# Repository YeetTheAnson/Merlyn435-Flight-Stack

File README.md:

# Merlyn435 Flight Stack

## Introduction
This is my custom Merlyn435 Flight Stack! This project was made as a successor to my previous Merlyn411 flight controller due to several limitations. It lacked in its processing power and free UART ports. Its mounting pattern was also unconventional at 25mm, making its mounting incompatible with any ESCs on the market. By upgrading to the AT32F435@288MHz, the new Merlyn435 easily handles 8k8 PID loop and advanced autonomous flights with 3 spare UART ports.

The Merlyn435 also upgrades the IMU from the MPU6500 to the LSM6DSK320X, which provides significantly better vibration noise rejection at $3.8\ \mathrm{mdps}/\sqrt{\mathrm{Hz}}$ compared to $10\ \mathrm{mdps}/\sqrt{\mathrm{Hz}}$. This results in cooler motors and more stable flights with fewer gyro filters, preventing issues such as mid throttle oscillation and flyaways.

The Merlyn435 flight controller is designed for a wide battery voltage ranging from 2 to 6 cells. This flight controller can also be mounted in various sizes of drones from 2" to as big as it can get.

It is a 3 in 1 flight controller offers features such as an integrated 2.4GHz ExpressLRS receiver and an OSD to overlay telemetry directly in the video feed. Furthermore, it has 16MB of flash memory for blackbox logging to assist in flight tuning.

The MerlynESC is a 4 in 1 ESC which runs on Bluejay firmware and also operates from 2 to 6s battery voltages. Its maximum continuous current is 40A per motor and peaks up to 55A for a maximum duration of 10 seconds.

| Feature | Merlyn435 | Merlyn411 |
|---|---|---|
| **MCU** | AT32F435CGU7 @ 288MHz | STM32F411CEU6 @ 100MHz |
| **MCU Flash Size** | 1024kB | 512kB |
| **UART Interfaces** | 5 Hardware UART (2 internal, 3 free) | 2 Hardware UART + 1 SoftSerial (1 internal, 1 softserial, 1 free) |
| **IMU** | LSM6DSK320X (SPI) | MPU6500 (SPI) |
| **Barometer** | BMP388 (I2C) | None |
| **OSD** | AT7456E (SPI) | AT7456E (SPI) |
| **Blackbox Flash** | 16MB (SPI) | 16MB (SPI) |
| **Integrated Receiver** | Serial ExpressLRS 2.4GHz  | Serial ExpressLRS 2.4GHz |
| **Mounting Size** | M2 20x20mm | M2 25.5x25.5mm |
| **BEC** | 5V 2A @ 1.1MHz Synchronous | 5V 2A @ 150kHz Asynchronous |
| **ESC Connection** | 8 pin JST-SH (Betaflight standard) | Direct solder pads |

## Hardware Specifications

### Merlyn435
* **MCU:** AT32F435CGU7
* **IMU:** LSM6DSK320X @ SPI1
* **Barometer:** BMP388 @ 0x76
* **OSD:** AT7456E @ SPI2
* **Blackbox:** W25Q128JV 16MB Flash @ SPI2
* **Receiver:** Serial ExpressLRS (ESP8285 + SX1281) @ UART2
* **Voltage range:** 2-6s LiPo / Li-ion / LiHV
* **Power Supply:** LMR51420YDDCR buck converter + SPX3819M5-L-3-3 LDO
* **Mounting:** M2 20x20mm

### MerlynESC
* **MCU:** EFM8BB21F16G
* **MOSFET:** JMSL0302AU
* **Gate Driver:** EG6288
* **Max Current:** 145A Peak / 40A Continuous @ 1.2mΩ
* **Voltage range:** 2-6s LiPo / Li-ion / LiHV
* **Power Supply:** HT75C0-1 12V LDO + HT7533-1 3.3V LDO
* **Mounting:** M2 20x20mm

## Pinout

| Header | Pin name | AT32 Pin | Description |
|---|---|---|---|
| **ESC** | `(1)BAT+` | - | Battery Positive Input from ESC |
| | `(2)GND` | - | Ground |
| | `(3)NC` | - | No Connection |
| | `(4)CURR` | PA1 | Current Sense Input |
| | `(5)M1` | PB6 | Motor 1 Signal Output |
| | `(6)M2` | PB7 | Motor 2 Signal Output |
| | `(7)M3` | PB0 | Motor 3 Signal Output |
| | `(8)M4` | PB1 | Motor 4 Signal Output |
| **GPS** | `C` | PH2 | I2C SCL (Internal BMP388 & External Magnetometer) |
| | `D` | PH3 | I2C SDA (Internal BMP388 & External Magnetometer) |
| | `T` | PB4 | UART7 TX |
| | `R` | PB3 | UART7 RX |
| | `G` | - | Ground |
| | `5` | - | 5V Power Output |
| **URT5** | `T` | PB9 | UART5 TX |
| | `R` | PB8 | UART5 RX |
| | `G` | - | Ground |
| | `5` | - | 5V Power Output |
| **CAM** | `I` | - | Analog Video Input |
| | `G` | - | Ground |
| | `5` | - | 5V Power Output |
| **URT3** | `5` | - | 5V Power Output |
| | `G` | - | Ground |
| | `R` | PB11 | UART3 RX |
| | `T` | PB10 | UART3 TX |
| **VTX** | `T` | PA9 | UART1 TX (IRC Tramp / SmartAudio) |
| | `O` | - | Analog Video Output (OSD Overlay) |
| | `G` | - | Ground |
| | `B+` | - | Battery Output for VTX |
| **BZ** | `-` | PC15 | Beeper MOSFET  Pin |
| | `+` | - | 5V Power Output |
| **POWER** | `3` | - | 3.3V Power Input/Output |
| | G | - | Ground |
| | `5` | - | 5V Power Input/Output |
| **Test Points** | `RX` | PA2 | UART2 TX (ExpressLRS RX) |
| | `TX` | PA3 | UART2 RX (ExpressLRS TX) |
| | `D` | PA13 | SWDIO (Debug & Flash) |
| | `C` | PA14 | SWCLK (Debug & Flash) |
| | `R` | NRST | NRST (Debug & Flash) |
| | `B` | BOOT0 | BOOT0 (Debug & Flash) |
| **Jumpers** | `BOOT` | ESP8285 GPIO0 | Bridge to enter ExpressLRS bootloader mode |
| | `RST` | ESP8285 CHIP_EN | Bridge to disable internal ExpressLRS receiver |

----

## Hardware Overview

### Merlyn435

### MerlynESC

----

## Flight Controller Firmware
Because the Merlyn435 is a custom hardware layout with no existing Betaflight targets, you must compile Betaflight using the custom target definitions in [/firmware/source/betaflight](https://github.com/YeetTheAnson/Merlyn435-Flight-Stack/tree/main/firmware/source/betaflight) or use the pre compiled firmware of your preferred Betaflight version in [/firmware/binaries](https://github.com/YeetTheAnson/Merlyn435-Flight-Stack/tree/main/firmware/binaries)

> [!IMPORTANT]
> The LSM6DSK320X was officially added in **v2026.6**. The same **Betaflight** configuration can be used to compile your binary for both **2025.12** and **2026.6** without any issues. However, **2025.12 does not support or detect the LSM6DSK320X**, so the **LSM6DSK320X** IMU will only function when running **2026.6 or later**.

### How to build the firmware (Betaflight)
1. Clone the [betaflight repository](https://github.com/betaflight/betaflight) using any UNIX terminal (use MSYS2 MINGW64 on Windows) and enter the directory
2. Enter `make configs` (install any required GCC toolchain if asked)
3. Create a directory in betaflight/src/config/configs named `MERLYN435` and paste [config.h](https://github.com/YeetTheAnson/Merlyn435-Flight-Stack/tree/main/firmware/source/betaflight/config.h) in the new directory
  - For v2026.6 and later, create a directory in configs named "ANSN" before creating the `MERLYN435` directory inside "ANSN"
4. Enter `make MERLYN435` and the `.hex` file should appear in `betaflight/obj`

### How to build the firmware (iNav)
1. Clone the [iNav repository](https://github.com/iNavFlight/inav) using any UNIX terminal (Building iNav is not supported on Windows) and enter the directory
2. Switch to the latest iNav stable release. E.g. `git checkout 9.1.0`
3. Create two directories. One named `build` in the root directory and another named `MERLYN435` in /src/main/target
4. Copy `CMakeLists.txt`, `target.c` and `target.h` into the `MERLYN435` directory from [/firmware/source/inav](https://github.com/YeetTheAnson/Merlyn435-Flight-Stack/tree/main/firmware/source/inav)
5. Enter the `build` directory
6. Enter `cmake ..` (install any required GCC toolchain if asked)
7. Enter `make MERLYN435` and the `.hex` file should appear in `/build`

### Flight Controller Flashing
1. **Via USB DFU Mode (Recommended):** Short the SWD `B` test point to 3.3v and plug in the USB C cable. Open [Betaflight Configurator](https://app.betaflight.com) (applicable for iNav), select your compiled local `.hex` file, and click Flash Firmware.
2. **Via SWD:** If the bootloader is corrupted, connect an ST Link programmer to the `B`, `D` and `C` test points (`R` is optional) and flash the compiled binary with STM32CubeProgrammer.

## ExpressLRS Flashing
The internal ESP8285 ExpressLRS receiver is wired to the AT32 via UART2. It uses the **BETAFPV 2.4GHz Lite RX** firmware target. The firmware binaries can be obtained from the ELRS [site](https://expresslrs.github.io/web-flasher/) or from this repository in [/firmware/binaries](https://github.com/YeetTheAnson/Merlyn435-Flight-Stack/blob/main/firmware/binaries/(ExpressLRS)MERLYN435_v4.10_FCC.bin). There are two way to flash the receiver:

### Method 1: Betaflight Passthrough
Note that Betaflight must be installed and configured before passthrough works.
1. Bridge the BOOT pad

2. Connect the FC via USB
3. Open the ExpressLRS Configurator [web flasher](https://expresslrs.github.io/web-flasher/) or app
4. Select `Receiver`
5. Select your preferred firmware version and the `BETAFPV 2.4GHz Lite RX` target and press next
6. [OPTIONAL] Enter your bind phrase
7. Select the Betaflight Passthrough flashing method, press next and follow the steps

### Method 2: Manual Flashing

If the ESP8285 is bricked or passthrough fails, you can flash it directly using an FTDI adapter or another ESP8285/ESP8286/ESP32 or even an Arduino. Bridge `R` to `GND` as well as the BOOT jumper and connect the FTDI TX to RX and FTDI RX to TX

## ESC Flashing

The MerlynESC is a 4 in 1 ESC that runs Bluejay firmware target `A`, MCU type `H`, `30`x20.4ns deadtime and `48`KHz PWM frequency. The firmware files can be found in [/firmware/binaries](https://github.com/YeetTheAnson/Merlyn435-Flight-Stack/blob/main/firmware/binaries/(Bluejay)A_H_30_48_v0.21.0.hex) or the official Bluejay repository. You can flash the EFM8BB21 chips using the C2 programming pads with a makeshift arduino programmer.

-----

## Drone Assembly

While this project is mainly focused on the Merlyn435 + MerlynESC flight stack, I also designed a high performance 3 inch freestyle FPV drone. If you want to recreate the full build, below is the component breakdown:

### Component List
* **Frame:** RATE S30 Pro carbon fiber frame
* **Motors:** RATE 1505 4300KV
* **Propellers:** HQProp 3x3x3
* **Camera:** Caddx Ratel 2 analog camera
* **VTX:** Cyclone 1W analog video transmitter
* **GPS:** RATE M10 GPS module
* **Battery:** GNB 4S 850mAh 120C LiHV
* **Fasteners (If using CF frame):** Included with frame kit
* **Fasteners (If using 3d printed frame):**
  * 6x M3 20mm Female to Female Brass Standoffs 
  * 12x M3 6mm Screws
  * 4x M2 Nuts
  * 4x M2 20mm Screws
  * 8x M2 10mm Screws
  * 16x M2 6mm Screws
  * 4x M2 6mm Screws
  * 8x M2 6mm Self Tapping Screws

### Why 3D Printing the Frame is Not Recommended
I advise against 3D printing your frame. On my previous build, a 100 percent infill PETG frame shattered from a very light fall. More importantly, 3D printed frames flex and resonate which causes excessive gyro noise and leads to deteriorated flight performance. 

https://github.com/user-attachments/assets/90db9ad2-082e-437a-b4b3-71ebe933a74a

### Assembly Instructions
The Merlyn435 and ESC uses standard 20x20mm mounting hole distance.

#### Stack Mounting
1. Place 4x M2 Nuts into the recesses in the bottom frame plate.

2. Push rubber grommets into the flight controller and ESC mounting holes.

3. Push 4x M2 20mm screws through the adapter plate, through the rubber grommet, and through 
the bottom plate into the M2 nuts.

#### VTX Mounting
The VTX mounts to the rear of the frame.
1. Place 4x M2 Nuts into the recesses in the bottom frame plate.

2. Push rubber grommets into the VTX mounting holes.

3. Push 4x M2 10mm screws through rubber grommets, down through the bottom plate, and into the M2 nuts.

#### Motor Mounting
1. Mount the four 1505 4300KV motors to the arms using 16x M2 6mm screws (4 per motor). Ensure the screws do not touch the motor windings inside the bell.

2. Mount the HQPROP 3x3x3 propellers. Pay attention to motor rotation directions (depending on your betaflight configuration, it could either be prop in or prop out). Fasten each prop with 2x M2 6mm screws.

#### Remaining Components
1. Mount the analog FPV camera to the cage using 2x M2 6mm screws.

2. Mount the camera cage to the bottom frame using 2x M2 6mm Self Tapping screws.

3. Mount the 6x M3 20mm Female to Female Brass Standoffs and secure with 6x M3 6mm screws to the bottom plate.

4. Press fit the antenna holder to the brass standoffs, then insert the antenna and connect the antenna to the VTX.

5. Press fit the GPS module into the bracket.

6. Mount the top plate and secure with 6x M3 6mm screws.

7. Mount the GPS module and bracket underneath the top plate and secure with 4x M2 6mm Self Tapping screws.

8. Insert 2x M2 6mm Self Tapping screws to secure the top plate to the camera cage.

----

## Bill of Material

Note: The prices in USD are converted as of 22 August 2026 and may fluctuate. Promo codes will be applied before checkout to bring the costs down. And yes, the costs of separate components are cheaper than JLCPCB assembly.

| Category | Item Name | Description | Link | Vendor | Quantity | Total Price (USD) |
|---|---|---|---|---|---:|---:|
| Flight Controller | TAXM8M4RDBCCT2T | 8 MHz crystal | [link](https://www.lcsc.com/product-detail/C400090.html) | LCSC | 5 | 0.73 |
| Flight Controller | 7D027000I01 | 27 MHz crystal | [link](https://www.lcsc.com/product-detail/C648952.html) | LCSC | 5 | 0.50 |
| Flight Controller | XL7EL89CMI-111YLC-26M | 26 MHz crystal | [link](https://www.lcsc.com/product-detail/C19272774.html) | LCSC | 5 | 0.44 |
| Flight Controller | XC21M4-52.000-F10NNHPL | 52 MHz crystal | [link](https://www.lcsc.com/product-detail/C3034316.html) | LCSC | 5 | 0.68 |
| Flight Controller | TYPE-C 16P QTWT | USB C Connector SMT | [link](https://www.lcsc.com/product-detail/C5187472.html) | LCSC | 10 | 0.75 |
| Flight Controller | LMR51420YDDCR | Buck converter | [link](https://www.lcsc.com/product-detail/C5383002.html) | LCSC | 2 | 1.96 |
| Flight Controller | AT7456E | Video overlay OSD | [link](https://www.lcsc.com/product-detail/C82351.html) | LCSC | 2 (Two because there's a deal on LCSC that lets me get both for free) | 7.49 |
| Flight Controller | SPX3819M5-L-3-3/TR | 3.3v LDO regulator | [link](https://www.lcsc.com/product-detail/C9055.html) | LCSC | 10 | 2.19 |
| Flight Controller | APH0420T4R7M | 4.7uH inductor | [link](https://www.lcsc.com/product-detail/C5349668.html) | LCSC | 5 | 0.45 |
| Flight Controller | USBLC6-2SC6 | USB ESD protection | [link](https://www.lcsc.com/product-detail/C7519.html) | LCSC | 5 | 0.92 |
| Flight Controller | BWU.FL-IPEX1 | U.FL connector | [link](https://www.lcsc.com/product-detail/C5137195.html) | LCSC | 10 | 0.42 |
| Flight Controller | 0402WGF1202TCE | 12k 0402 resistor | [link](https://www.lcsc.com/product-detail/C25752.html) | LCSC | 100 | 0.69 |
| Flight Controller | 0402WGF1501TCE | 1.5k 0402 resistor | [link](https://www.lcsc.com/product-detail/C25867.html) | LCSC | 100 | 0.50 |
| Flight Controller+ESC | CL10A106MA8NRNC | 10uF 0603 capacitor | [link](https://www.lcsc.com/product-detail/C96446.html) | LCSC | 20 | 1.60 |
| Flight Controller | 1206B475K500NT | 4.7uF 1206 capacitor | [link](https://www.lcsc.com/product-detail/C29823.html) | LCSC | 10 | 2.72 |
| Flight Controller | W25Q128JVSIQ | 16MB flash chip | [link](https://www.lcsc.com/product-detail/C97521.html) | LCSC | 1 | 2.62 |
| Flight Controller | HC-1.0-8PWT | JST SH 8p connector | [link](https://www.lcsc.com/product-detail/C2845367.html) | LCSC | 5 | 0.67 |
| Flight Controller | LSM6DSK320XTR | LSM6 series IMU | [link](https://www.lcsc.com/product-detail/C53025794.html) | LCSC | 1 | 9.18 |
| Flight Controller | PCB | PCB | - | JLCPCB | 1 | 7.00 |
| Flight Controller | Partial PCB Assembly | Partial PCB Assembly | - | JLCPCB | 1 | 47.91 |
| ESC | GRM21BR61H106KE43L | 10uF 0805 capacitor | [link](https://www.lcsc.com/product-detail/C440198.html) | LCSC | 5 | 1.25 |
| ESC | CL31A106KBHNNNE | 10uF 1206 capacitor | [link](https://www.lcsc.com/product-detail/C13585.html) | LCSC | 20 | 5.63 |
| ESC | CL05B104KB54PNC | 0.1uF 0402 capacitor | [link](https://www.lcsc.com/product-detail/C307331.html) | LCSC | 100 | 0.93 |
| ESC | CL05A105KA5NQNC | 1uF 0402 capacitor | [link](https://www.lcsc.com/product-detail/C52923.html) | LCSC | 50 | 0.61 |
| ESC | 1SS400CMT2R | SOD923 diode | [link](https://www.lcsc.com/product-detail/C510311.html) | LCSC | 40 | 1.02 |
| ESC | JMSL0302AU | N channel MOSFET | [link](https://www.lcsc.com/product-detail/C2890409.html) | LCSC | 25 | 7.07 |
| ESC | 0402WGF1002TCE | 10k 0402 resistor | [link](https://www.lcsc.com/product-detail/C25744.html) | LCSC | 100 | 0.19 |
| ESC | 0402WGF4701TCE | 4.7k 0402 resistor | [link](https://www.lcsc.com/product-detail/C25900.html) | LCSC | 100 | 0.50 |
| ESC | 0402WGF1001TCE | 1k 0402 resistor | [link](https://www.lcsc.com/product-detail/C11702.html) | LCSC | 100 | 0.67 |
| ESC | 0402WGF100JTCE | 10R 0402 resistor | [link](https://www.lcsc.com/product-detail/C25077.html) | LCSC | 100 | 0.58 |
| ESC | HoYLR2512E-3W-0.5mR-1% | 0.5mR 2512 shunt resistor | [link](https://www.lcsc.com/product-detail/C5375456.html) | LCSC | 10 | 0.60 |
| ESC | 0402WGF3902TCE | 39k 0402 resistor | [link](https://www.lcsc.com/product-detail/C25783.html) | LCSC | 100 | 0.69 |
| ESC | HT75C0-1 | 12v LDO regulator | [link](https://www.lcsc.com/product-detail/C64551.html) | LCSC | 5 | 0.99 |
| ESC | HT7533-1 | 3.3v LDO regulator | [link](https://www.lcsc.com/product-detail/C14289.html) | LCSC | 5 | 0.71 |
| ESC | EFM8BB21F16G-C-QFN20R | ESC MCU | [link](https://www.lcsc.com/product-detail/C80713.html) | LCSC | 5 | 6.33 |
| ESC | EG6288 | Gate driver | [link](https://www.lcsc.com/product-detail/C55058511.html) | LCSC | 10 | 3.06 |
| ESC | INA139NA/3K | Current sensor | [link](https://www.lcsc.com/product-detail/C129947.html) | LCSC | 2 | 1.12 |
| ESC | PCB | PCB | - | JLCPCB | 1 | 2.00 |
| Flight Controller + ESC | Shipping | EPOST shipping | - | JLCPCB | 1 | 6.49 |
| Flight Controller + ESC | Shipping | LCSC | - | LCSC | 1 | 4.92 |
| Drone Parts | RATE 1505 4300kv motor | Motors | [link](https://click.world.taobao.com/_b.RcEIyQ) | TaoBao | 4 | 28.75 |
| Drone Parts | RATE S30 Pro frame | Carbon fiber frame | [link](https://click.world.taobao.com/_b.6cEImS) | TaoBao | 1 | 23.06 |
| Drone Parts | RATE analog antenna | Right hand circular polarized 5.8GHz antenna | [link](https://click.world.taobao.com/_b.ecEImU) | TaoBao | 1 | 5.80 |
| Drone Parts | RATE 90mm ELRS antenna | Linear polarized dipole 2.4GHz antenna | [link](https://click.world.taobao.com/_b.3cEIO4) | TaoBao | 1 | 0.95 |
| Drone Parts | RATE beeper/buzzer | Active piezo buzzer | [link](https://click.world.taobao.com/_b.VcEIzD) | TaoBao | 1 | 0.64 |
| Drone Parts | HQPROP T3x3x3 | 2 Pairs 3 inch propeller | [link](https://click.world.taobao.com/_b.0cEJ5z) | TaoBao | 1 | 1.88 |
| Drone Parts | RATE XT30 + Cable | Connector and cable | [link](https://click.world.taobao.com/_b.acEJqe) | TaoBao | 1 | 0.64 |
| Drone Parts | RATE Rubber Grommets | 10pcs soft mounting rubber grommet | [link](https://click.world.taobao.com/_b.KcEIzp) | TaoBao | 1 | 0.48 |
| Drone Parts | RATE M10 GPS | Nano size gps module with battery | [link](https://click.world.taobao.com/_b.tcEIm7) | TaoBao | 1 | 8.80 |
| Drone Parts | 470uF low ESR capacitor | Capacitor for MOSFET protection | [link](https://click.world.taobao.com/_b.ecEuQ7) | TaoBao | 1 | 0.42 |
| Drone Parts | Cyclone 1W VTX | 5.8GHz analog video transmitter | [link](https://click.world.taobao.com/_b.zcEIzr) | TaoBao | 1 | 14.00 |
| Drone Parts | TaoBao Tax | Fees | - | TaoBao | 1 | 10.05 |
| Drone Parts | TaoBao Shipping | Shipping | - | TaoBao | 1 | 4.05 |
| Drone Parts | CADDX Ratel 2 + Tax | 19mm Analog camera | [link](https://www.aliexpress.com/item/1005009304280288.html) | AliExpress | 1 | 28.64 |
| Drone Parts | AliExpress Shipping | Shipping | - | AliExpress | 1 | 0.99 |
| Drone Parts | GNB LiHV 4S 850mAh | 4S LiHV battery | [link](https://shopee.com.my/Gaoneng-GNB-15.2HV-850mAh-120C-4S-Lipo-Battery-with-XT30-Plug-GNB850-120-4S-i.92575144.18545880487) | Shopee | 1 | 20.10 |

- **Flight Controller Total:** $89.42
- **ESC Total:** $33.95
- **Shipping Total:** $26.50
- **Drone Parts Total:** $134.16
### **Grand Total:** $284.03

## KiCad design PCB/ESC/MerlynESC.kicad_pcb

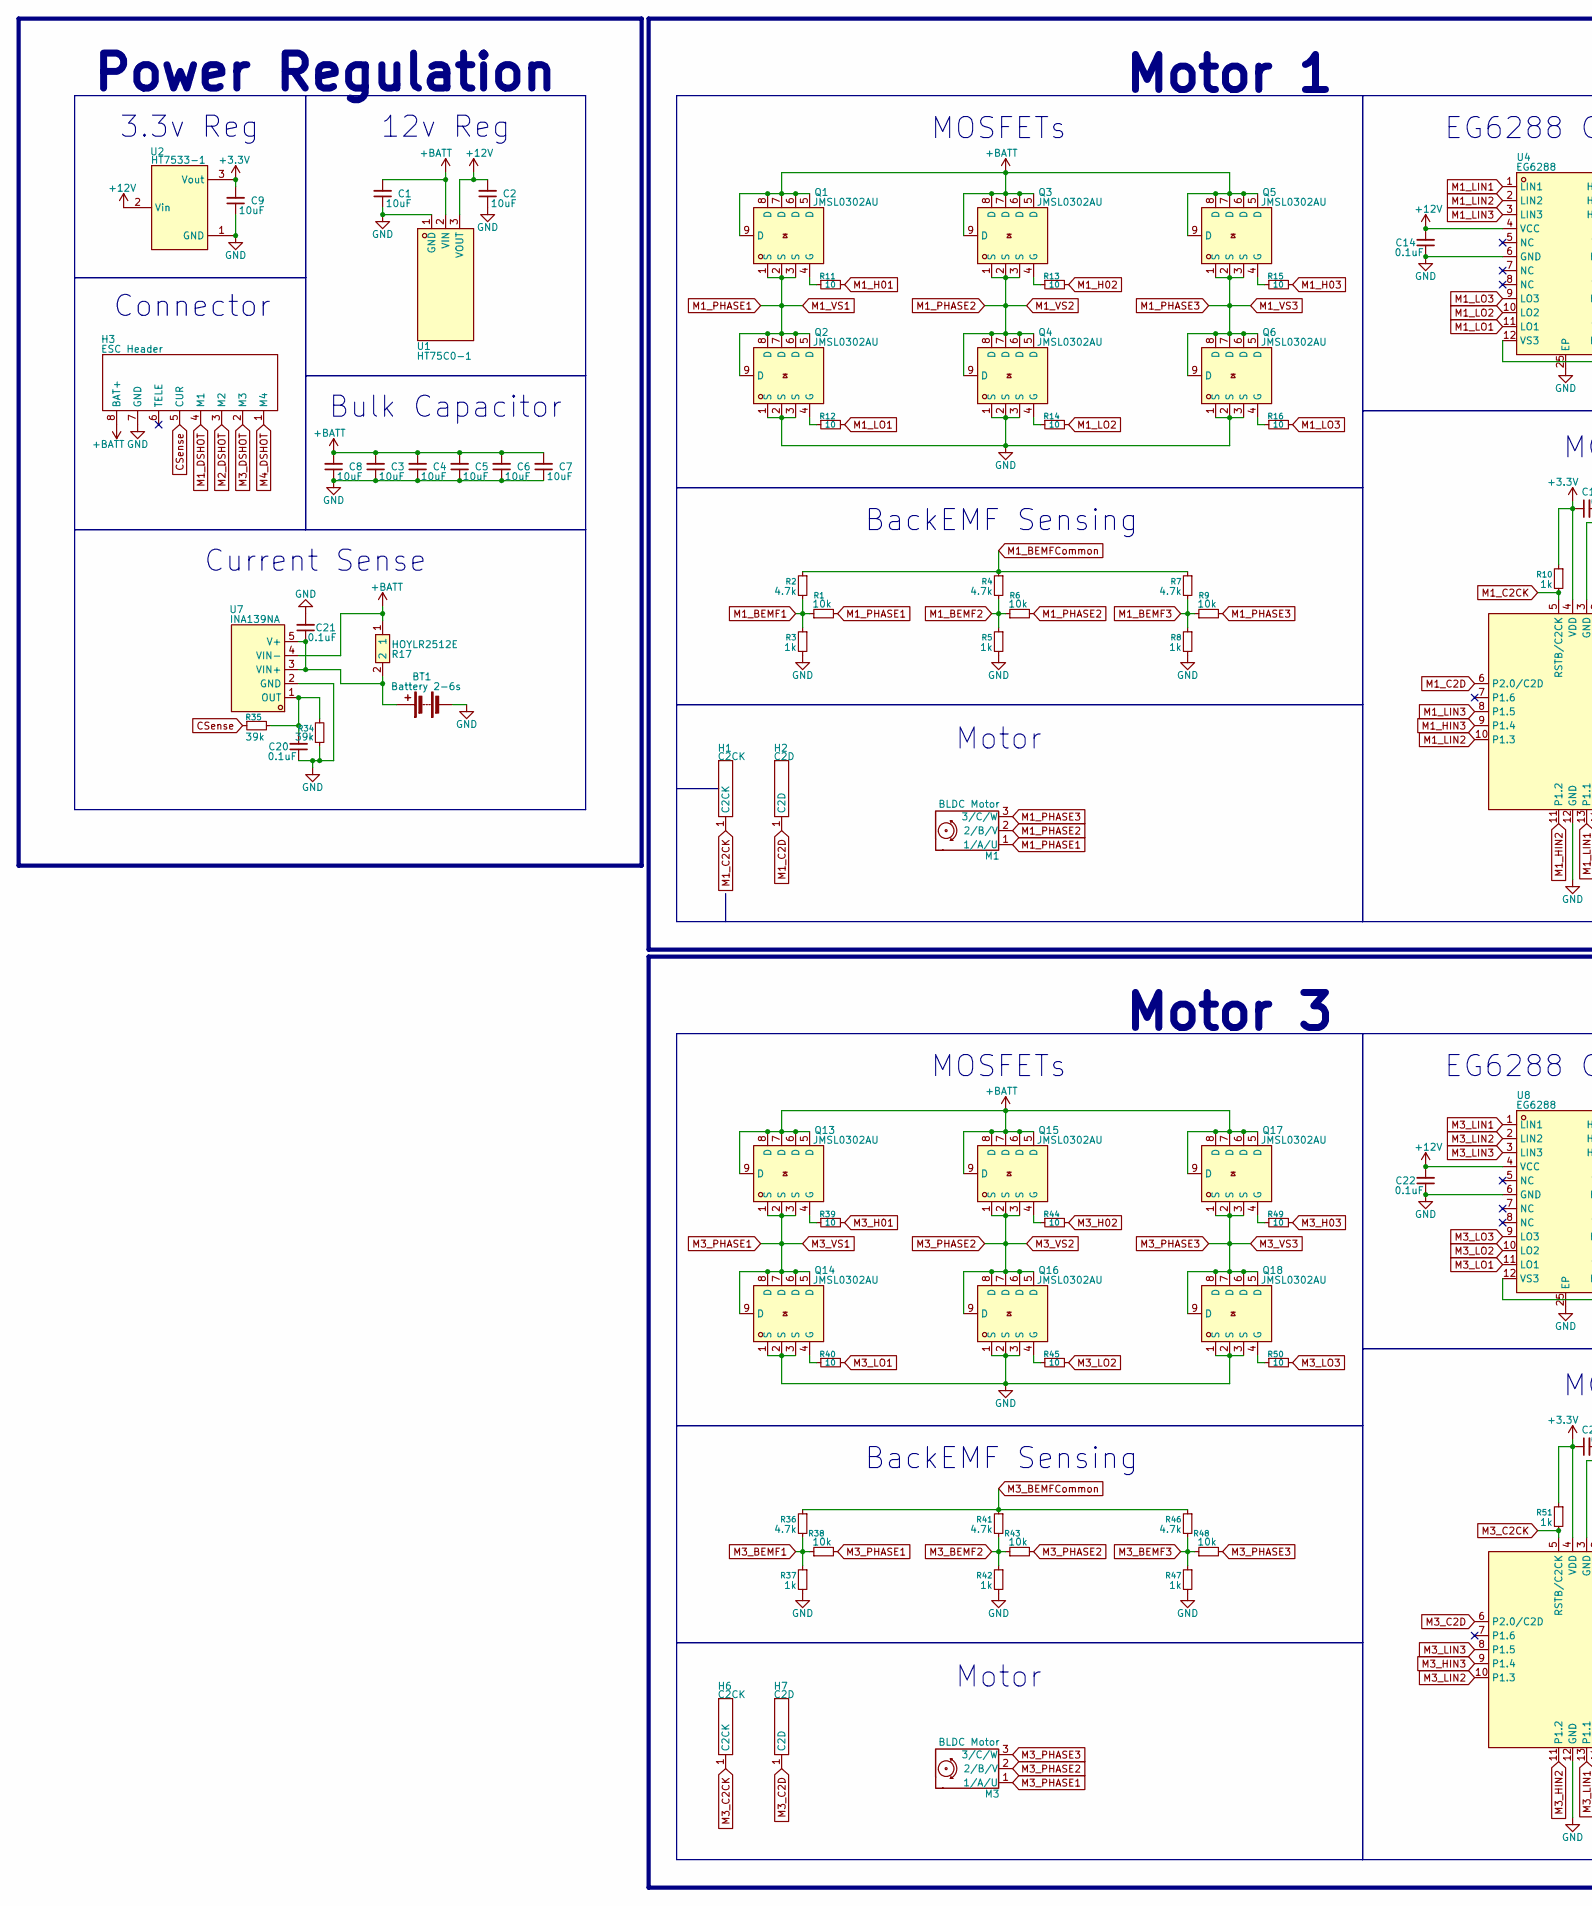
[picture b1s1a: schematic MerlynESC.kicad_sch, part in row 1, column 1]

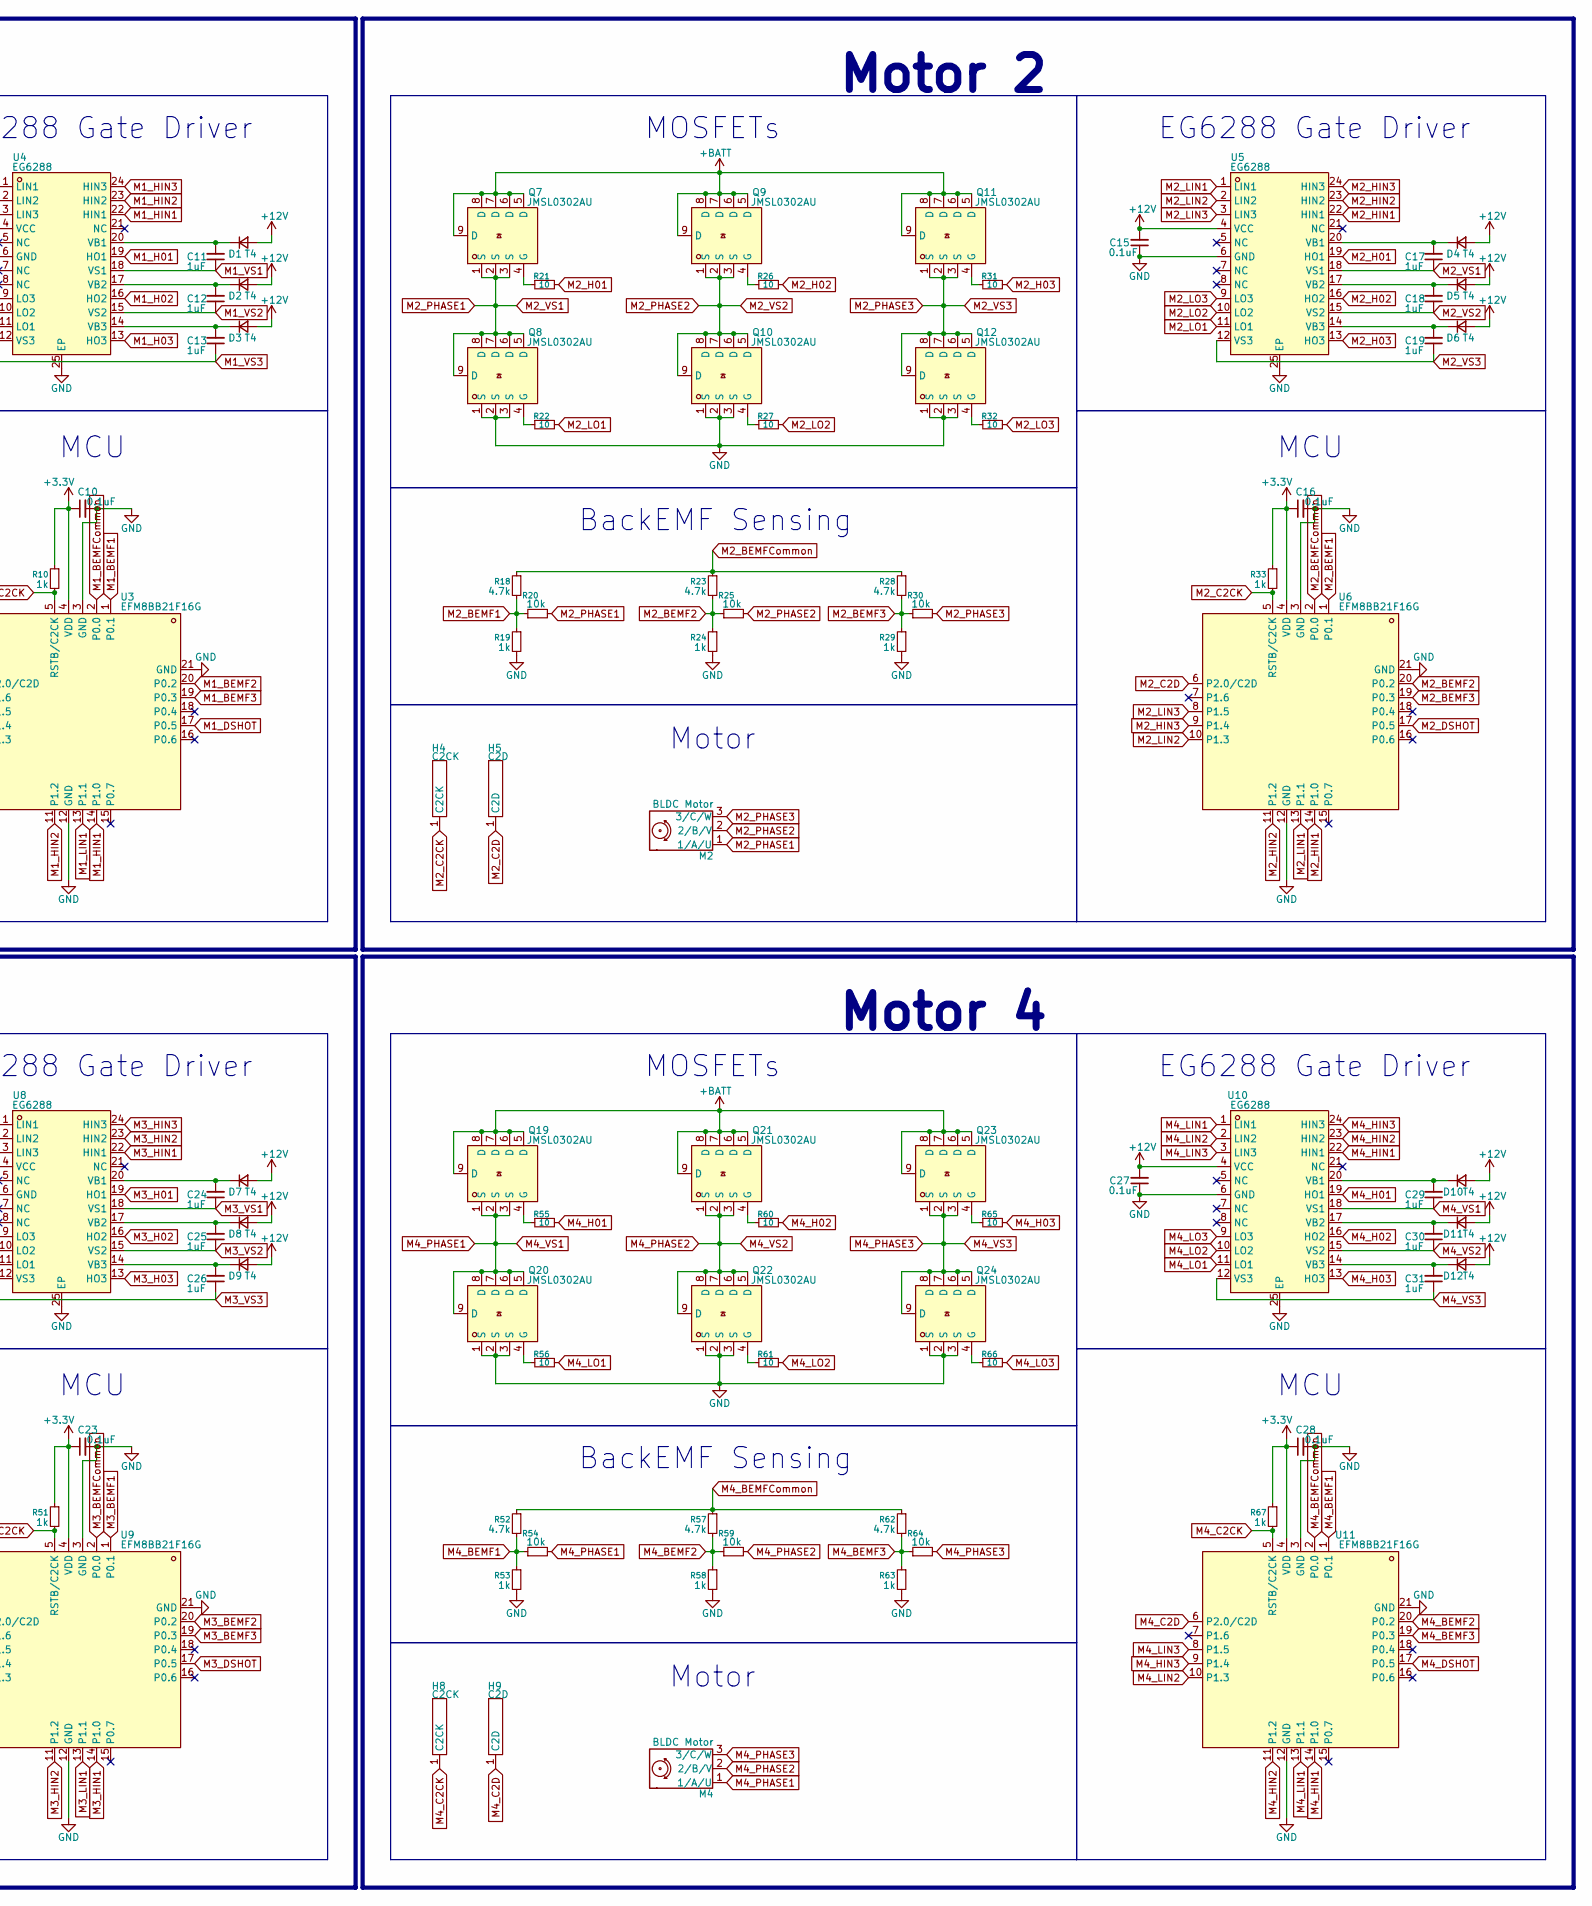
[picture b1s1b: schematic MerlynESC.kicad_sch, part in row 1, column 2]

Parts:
BT1: Battery 2-6s; PowerPad
C1: 10uF; C_0805_2012Metric; LCSC Part C440198
C2, C9: 10uF; C_0603_1608Metric; LCSC Part C96446
C3, C4, C5, C6, C7, C8: 10uF; C_1206_3216Metric; LCSC Part C13585
C10, C14, C15, C16, C20, C21, C22, C23, C27, C28: 0.1uF; C_0402_1005Metric; LCSC Part C307331
C11, C12, C13, C17, C18, C19, C24, C25, C26, C29, C30, C31: 1uF; C_0402_1005Metric; LCSC Part C52923
D1, D2, D3, D4, D5, D6, D7, D8, D9, D10, D11, D12: T4; D_SOD-923; LCSC Part C510311
H1, H4, H6, H8: C2CK; TestPoint
H2, H5, H7, H9: C2D; TestPoint
H3: ESC Header
M1, M2, M3, M4: BLDC Motor; MotorPad
Q1, Q2, Q3, Q4, Q5, Q6, Q7, Q8, Q9, Q10, Q11, Q12, Q13, Q14, Q15, Q16, Q17, Q18, Q19, Q20, Q21, Q22, Q23, Q24: JMSL0302AU; DFN-8_L3.2-W3.1-P0.65-LS3.4-BL; MPN JMSL0302AU; LCSC Part C2890409
R1, R6, R9, R20, R25, R30, R38, R43, R48, R54, R59, R64: 10k; R_0402_1005Metric; LCSC Part C25744
R2, R4, R7, R18, R23, R28, R36, R41, R46, R52, R57, R62: 4.7k; R_0402_1005Metric; LCSC Part C25900
R3, R5, R8, R10, R19, R24, R29, R33, R37, R42, R47, R51, R53, R58, R63, R67: 1k; R_0402_1005Metric; LCSC Part C11702
R11, R12, R13, R14, R15, R16, R21, R22, R26, R27, R31, R32, R39, R40, R44, R45, R49, R50, R55, R56, R60, R61, R65, R66: 10; R_0402_1005Metric; LCSC Part C25077
R17: HOYLR2512E; R2512; MPN HoYLR2512E-3W-0.5mR-1%; LCSC Part C5375456
R34, R35: 39k; R_0402_1005Metric; LCSC Part C25783
U1: HT75C0-1; SOT-89-3_L4.5-W2.5-P1.50-LS4.2-BR; MPN HT75C0-1; LCSC Part C64551
U2: HT7533-1; SOT-89-3_L4.5-W2.5-P1.50-LS4.2-BR; MPN HT7533-1; LCSC Part C14289
U3, U6, U9, U11: EFM8BB21F16G; QFN-20_L3.0-W3.0-P0.50-BL-EP1.7_EFM8BB21F16G; MPN EFM8BB21F16G-C-QFN20R; LCSC Part C80713
U4, U5, U8, U10: EG6288; QFN-24_L4.0-W4.0-P0.50-TL-EP2.6; MPN EG6288; LCSC Part C55058511
U7: INA139NA; SOT-23-5_L3.0-W1.7-P0.95-LS2.8-BR; MPN INA139NA/3K; LCSC Part C129947

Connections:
+3.3V: C9.2, C10.1, C16.1, C23.1, C28.1, R10.1, R33.1, R51.1, R67.1, U2.3 (Vout), U3.4 (VDD), U6.4 (VDD), U9.4 (VDD), U11.4 (VDD)
+12V: C2.2, C14.2, C15.2, C22.2, C27.2, D1.2 (A), D2.2 (A), D3.2 (A), D4.2 (A), D5.2 (A), D6.2 (A), D7.2 (A), D8.2 (A), D9.2 (A), D10.2 (A), D11.2 (A), D12.2 (A), U1.3 (VOUT), U2.2 (Vin), U4.4 (VCC), U5.4 (VCC), U8.4 (VCC), U10.4 (VCC)
+BATT: C1.2, C3.2, C4.2, C5.2, C6.2, C7.2, C8.2, H3.8 (BAT+), Q1.5 (D), Q1.6 (D), Q1.7 (D), Q1.8 (D), Q1.9 (D), Q3.5 (D), Q3.6 (D), Q3.7 (D), Q3.8 (D), Q3.9 (D), Q5.5 (D), Q5.6 (D), Q5.7 (D), Q5.8 (D), Q5.9 (D), Q7.5 (D), Q7.6 (D), Q7.7 (D), Q7.8 (D), Q7.9 (D), Q9.5 (D), Q9.6 (D), Q9.7 (D), Q9.8 (D), Q9.9 (D), Q11.5 (D), Q11.6 (D), Q11.7 (D), Q11.8 (D), Q11.9 (D), Q13.5 (D), Q13.6 (D), Q13.7 (D), Q13.8 (D), Q13.9 (D), Q15.5 (D), Q15.6 (D), Q15.7 (D), Q15.8 (D), Q15.9 (D), Q17.5 (D), Q17.6 (D), Q17.7 (D), Q17.8 (D), Q17.9 (D), Q19.5 (D), Q19.6 (D), Q19.7 (D), Q19.8 (D), Q19.9 (D), Q21.5 (D), Q21.6 (D), Q21.7 (D), Q21.8 (D), Q21.9 (D), Q23.5 (D), Q23.6 (D), Q23.7 (D), Q23.8 (D), Q23.9 (D), R17.1, U1.2 (VIN), U7.4 (VIN-)
CSense: H3.5 (CUR), R35.1
GND: BT1.2 (-), C1.1, C2.1, C3.1, C4.1, C5.1, C6.1, C7.1, C8.1, C9.1, C10.2, C14.1, C15.1, C16.2, C20.1, C21.2, C22.1, C23.2, C27.1, C28.2, H3.7 (GND), Q2.1 (S), Q2.2 (S), Q2.3 (S), Q4.1 (S), Q4.2 (S), Q4.3 (S), Q6.1 (S), Q6.2 (S), Q6.3 (S), Q8.1 (S), Q8.2 (S), Q8.3 (S), Q10.1 (S), Q10.2 (S), Q10.3 (S), Q12.1 (S), Q12.2 (S), Q12.3 (S), Q14.1 (S), Q14.2 (S), Q14.3 (S), Q16.1 (S), Q16.2 (S), Q16.3 (S), Q18.1 (S), Q18.2 (S), Q18.3 (S), Q20.1 (S), Q20.2 (S), Q20.3 (S), Q22.1 (S), Q22.2 (S), Q22.3 (S), Q24.1 (S), Q24.2 (S), Q24.3 (S), R3.2, R5.2, R8.2, R19.2, R24.2, R29.2, R34.1, R37.2, R42.2, R47.2, R53.2, R58.2, R63.2, U1.1 (GND), U2.1 (GND), U3.3 (GND), U3.12 (GND), U3.21 (GND), U4.6 (GND), U4.25 (EP), U5.6 (GND), U5.25 (EP), U6.3 (GND), U6.12 (GND), U6.21 (GND), U7.2 (GND), U8.6 (GND), U8.25 (EP), U9.3 (GND), U9.12 (GND), U9.21 (GND), U10.6 (GND), U10.25 (EP), U11.3 (GND), U11.12 (GND), U11.21 (GND)
M1_BEMF1: R1.1, R2.2, R3.1, U3.1 (P0.1)
M1_BEMF2: R4.2, R5.1, R6.1, U3.20 (P0.2)
M1_BEMF3: R7.2, R8.1, R9.1, U3.19 (P0.3)
M1_BEMFCommon: R2.1, R4.1, R7.1, U3.2 (P0.0)
M1_C2CK: H1.1 (C2CK), R10.2, U3.5 (RSTB/C2CK)
M1_C2D: H2.1 (C2D), U3.6 (P2.0/C2D)
M1_DSHOT: H3.4 (M1), U3.17 (P0.5)
M1_H01: R11.2, U4.19 (HO1)
M1_H02: R13.2, U4.16 (HO2)
M1_H03: R15.2, U4.13 (HO3)
M1_HIN1: U3.14 (P1.0), U4.22 (HIN1)
M1_HIN2: U3.11 (P1.2), U4.23 (HIN2)
M1_HIN3: U3.9 (P1.4), U4.24 (HIN3)
M1_LIN1: U3.13 (P1.1), U4.1 (LIN1)
M1_LIN2: U3.10 (P1.3), U4.2 (LIN2)
M1_LIN3: U3.8 (P1.5), U4.3 (LIN3)
M1_LO1: R12.2, U4.11 (LO1)
M1_LO2: R14.2, U4.10 (LO2)
M1_LO3: R16.2, U4.9 (LO3)
M1_PHASE1: C11.1, M1.1 (1/A/U), Q1.1 (S), Q1.2 (S), Q1.3 (S), Q2.5 (D), Q2.6 (D), Q2.7 (D), Q2.8 (D), Q2.9 (D), R1.2, U4.18 (VS1)
M1_PHASE2: C12.1, M1.2 (2/B/V), Q3.1 (S), Q3.2 (S), Q3.3 (S), Q4.5 (D), Q4.6 (D), Q4.7 (D), Q4.8 (D), Q4.9 (D), R6.2, U4.15 (VS2)
M1_PHASE3: C13.1, M1.3 (3/C/W), Q5.1 (S), Q5.2 (S), Q5.3 (S), Q6.5 (D), Q6.6 (D), Q6.7 (D), Q6.8 (D), Q6.9 (D), R9.2, U4.12 (VS3)
M2_BEMF1: R18.2, R19.1, R20.1, U6.1 (P0.1)
M2_BEMF2: R23.2, R24.1, R25.1, U6.20 (P0.2)
M2_BEMF3: R28.2, R29.1, R30.1, U6.19 (P0.3)
M2_BEMFCommon: R18.1, R23.1, R28.1, U6.2 (P0.0)
M2_C2CK: H4.1 (C2CK), R33.2, U6.5 (RSTB/C2CK)
M2_C2D: H5.1 (C2D), U6.6 (P2.0/C2D)
M2_DSHOT: H3.3 (M2), U6.17 (P0.5)
M2_H01: R21.2, U5.19 (HO1)
M2_H02: R26.2, U5.16 (HO2)
M2_H03: R31.2, U5.13 (HO3)
M2_HIN1: U5.22 (HIN1), U6.14 (P1.0)
M2_HIN2: U5.23 (HIN2), U6.11 (P1.2)
M2_HIN3: U5.24 (HIN3), U6.9 (P1.4)
M2_LIN1: U5.1 (LIN1), U6.13 (P1.1)
M2_LIN2: U5.2 (LIN2), U6.10 (P1.3)
M2_LIN3: U5.3 (LIN3), U6.8 (P1.5)
M2_LO1: R22.2, U5.11 (LO1)
M2_LO2: R27.2, U5.10 (LO2)
M2_LO3: R32.2, U5.9 (LO3)
M2_PHASE1: C17.1, M2.1 (1/A/U), Q7.1 (S), Q7.2 (S), Q7.3 (S), Q8.5 (D), Q8.6 (D), Q8.7 (D), Q8.8 (D), Q8.9 (D), R20.2, U5.18 (VS1)
M2_PHASE2: C18.1, M2.2 (2/B/V), Q9.1 (S), Q9.2 (S), Q9.3 (S), Q10.5 (D), Q10.6 (D), Q10.7 (D), Q10.8 (D), Q10.9 (D), R25.2, U5.15 (VS2)
M2_PHASE3: C19.1, M2.3 (3/C/W), Q11.1 (S), Q11.2 (S), Q11.3 (S), Q12.5 (D), Q12.6 (D), Q12.7 (D), Q12.8 (D), Q12.9 (D), R30.2, U5.12 (VS3)
M3_BEMF1: R36.2, R37.1, R38.1, U9.1 (P0.1)
M3_BEMF2: R41.2, R42.1, R43.1, U9.20 (P0.2)
M3_BEMF3: R46.2, R47.1, R48.1, U9.19 (P0.3)
M3_BEMFCommon: R36.1, R41.1, R46.1, U9.2 (P0.0)
M3_C2CK: H6.1 (C2CK), R51.2, U9.5 (RSTB/C2CK)
M3_C2D: H7.1 (C2D), U9.6 (P2.0/C2D)
M3_DSHOT: H3.2 (M3), U9.17 (P0.5)
M3_H01: R39.2, U8.19 (HO1)
M3_H02: R44.2, U8.16 (HO2)
M3_H03: R49.2, U8.13 (HO3)
M3_HIN1: U8.22 (HIN1), U9.14 (P1.0)
M3_HIN2: U8.23 (HIN2), U9.11 (P1.2)
M3_HIN3: U8.24 (HIN3), U9.9 (P1.4)
M3_LIN1: U8.1 (LIN1), U9.13 (P1.1)
M3_LIN2: U8.2 (LIN2), U9.10 (P1.3)
M3_LIN3: U8.3 (LIN3), U9.8 (P1.5)
M3_LO1: R40.2, U8.11 (LO1)
M3_LO2: R45.2, U8.10 (LO2)
M3_LO3: R50.2, U8.9 (LO3)
M3_PHASE1: C24.1, M3.1 (1/A/U), Q13.1 (S), Q13.2 (S), Q13.3 (S), Q14.5 (D), Q14.6 (D), Q14.7 (D), Q14.8 (D), Q14.9 (D), R38.2, U8.18 (VS1)
M3_PHASE2: C25.1, M3.2 (2/B/V), Q15.1 (S), Q15.2 (S), Q15.3 (S), Q16.5 (D), Q16.6 (D), Q16.7 (D), Q16.8 (D), Q16.9 (D), R43.2, U8.15 (VS2)
M3_PHASE3: C26.1, M3.3 (3/C/W), Q17.1 (S), Q17.2 (S), Q17.3 (S), Q18.5 (D), Q18.6 (D), Q18.7 (D), Q18.8 (D), Q18.9 (D), R48.2, U8.12 (VS3)
M4_BEMF1: R52.2, R53.1, R54.1, U11.1 (P0.1)
M4_BEMF2: R57.2, R58.1, R59.1, U11.20 (P0.2)
M4_BEMF3: R62.2, R63.1, R64.1, U11.19 (P0.3)
M4_BEMFCommon: R52.1, R57.1, R62.1, U11.2 (P0.0)
M4_C2CK: H8.1 (C2CK), R67.2, U11.5 (RSTB/C2CK)
M4_C2D: H9.1 (C2D), U11.6 (P2.0/C2D)
M4_DSHOT: H3.1 (M4), U11.17 (P0.5)
M4_H01: R55.2, U10.19 (HO1)
M4_H02: R60.2, U10.16 (HO2)
M4_H03: R65.2, U10.13 (HO3)
M4_HIN1: U10.22 (HIN1), U11.14 (P1.0)
M4_HIN2: U10.23 (HIN2), U11.11 (P1.2)
M4_HIN3: U10.24 (HIN3), U11.9 (P1.4)
M4_LIN1: U10.1 (LIN1), U11.13 (P1.1)
M4_LIN2: U10.2 (LIN2), U11.10 (P1.3)
M4_LIN3: U10.3 (LIN3), U11.8 (P1.5)
M4_LO1: R56.2, U10.11 (LO1)
M4_LO2: R61.2, U10.10 (LO2)
M4_LO3: R66.2, U10.9 (LO3)
M4_PHASE1: C29.1, M4.1 (1/A/U), Q19.1 (S), Q19.2 (S), Q19.3 (S), Q20.5 (D), Q20.6 (D), Q20.7 (D), Q20.8 (D), Q20.9 (D), R54.2, U10.18 (VS1)
M4_PHASE2: C30.1, M4.2 (2/B/V), Q21.1 (S), Q21.2 (S), Q21.3 (S), Q22.5 (D), Q22.6 (D), Q22.7 (D), Q22.8 (D), Q22.9 (D), R59.2, U10.15 (VS2)
M4_PHASE3: C31.1, M4.3 (3/C/W), Q23.1 (S), Q23.2 (S), Q23.3 (S), Q24.5 (D), Q24.6 (D), Q24.7 (D), Q24.8 (D), Q24.9 (D), R64.2, U10.12 (VS3)
unnamed: BT1.1 (+), C21.1, R17.2, U7.3 (VIN+), U7.5 (V+)
unnamed: C11.2, D1.1 (K), U4.20 (VB1)
unnamed: C12.2, D2.1 (K), U4.17 (VB2)
unnamed: C13.2, D3.1 (K), U4.14 (VB3)
unnamed: C17.2, D4.1 (K), U5.20 (VB1)
unnamed: C18.2, D5.1 (K), U5.17 (VB2)
unnamed: C19.2, D6.1 (K), U5.14 (VB3)
unnamed: C24.2, D7.1 (K), U8.20 (VB1)
unnamed: C25.2, D8.1 (K), U8.17 (VB2)
unnamed: C26.2, D9.1 (K), U8.14 (VB3)
unnamed: C29.2, D10.1 (K), U10.20 (VB1)
unnamed: C30.2, D11.1 (K), U10.17 (VB2)
unnamed: C31.2, D12.1 (K), U10.14 (VB3)
unnamed: Q1.4 (G), R11.1
unnamed: Q2.4 (G), R12.1
unnamed: Q3.4 (G), R13.1
unnamed: Q4.4 (G), R14.1
unnamed: Q5.4 (G), R15.1
unnamed: Q6.4 (G), R16.1
unnamed: Q7.4 (G), R21.1
unnamed: Q8.4 (G), R22.1
unnamed: Q9.4 (G), R26.1
unnamed: Q10.4 (G), R27.1
unnamed: Q11.4 (G), R31.1
unnamed: Q12.4 (G), R32.1
unnamed: Q13.4 (G), R39.1
unnamed: Q14.4 (G), R40.1
unnamed: Q15.4 (G), R44.1
unnamed: Q16.4 (G), R45.1
unnamed: Q17.4 (G), R49.1
unnamed: Q18.4 (G), R50.1
unnamed: Q19.4 (G), R55.1
unnamed: Q20.4 (G), R56.1
unnamed: Q21.4 (G), R60.1
unnamed: Q22.4 (G), R61.1
unnamed: Q23.4 (G), R65.1
unnamed: Q24.4 (G), R66.1
unnamed: C20.2, R34.2, R35.2, U7.1 (OUT)

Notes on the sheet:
Connector
Motor
12v Reg
MOSFETs
Motor 3
MCU
EG6288 Gate Driver
Current Sense
BackEMF Sensing
3.3v Reg
Motor 1
Motor 4
Bulk Capacitor
Power Regulation
Motor 2

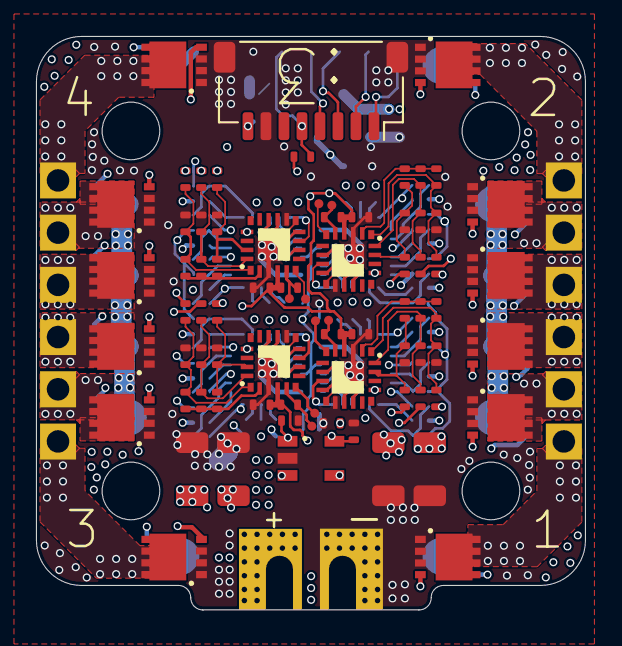
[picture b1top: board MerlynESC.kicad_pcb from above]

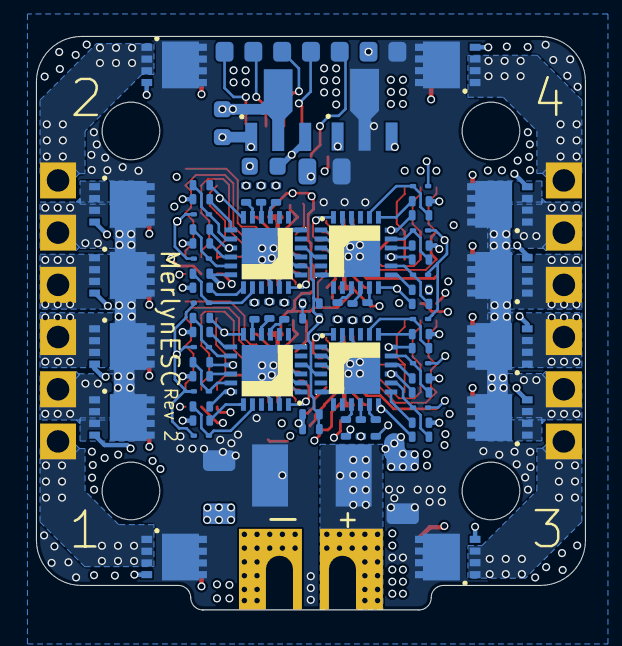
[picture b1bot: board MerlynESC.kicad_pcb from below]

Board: 6 copper layers, 30.5 x 31.9 mm, 159 parts (76 on the bottom side), 131 nets.

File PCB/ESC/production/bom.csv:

Designator,Footprint,Quantity,Value,LCSC Part #
BT1,PowerPad,1,Battery 2-6s,
C1,0805,1,10uF,C440198
"C10, C14, C15, C16, C20, C21, C22, C23, C27, C28",0402,10,0.1uF,C307331
"C11, C12, C13, C17, C18, C19, C24, C25, C26, C29, C30, C31",0402,12,1uF,C52923
"C2, C9",0603,2,10uF,C96446
"C3, C4, C5, C6, C7, C8",1206,6,10uF,C13585
"D1, D10, D11, D12, D2, D3, D4, D5, D6, D7, D8, D9",D_SOD-923,12,T4,C510311
H3,ESC Header,1,ESC Header,
"M1, M2, M3, M4",MotorPad,4,BLDC Motor,
"Q1, Q10, Q11, Q12, Q13, Q14, Q15, Q16, Q17, Q18, Q19, Q2, Q20, Q21, Q22, Q23, Q24, Q3, Q4, Q5, Q6, Q7, Q8, Q9",DFN-8_L3.2-W3.1-P0.65-LS3.4-BL,24,JMSL0302AU,C2890409
"R1, R20, R25, R30, R38, R43, R48, R54, R59, R6, R64, R9",0402,12,10k,C25744
"R10, R19, R24, R29, R3, R33, R37, R42, R47, R5, R51, R53, R58, R63, R67, R8",0402,16,1k,C11702
"R11, R12, R13, R14, R15, R16, R21, R22, R26, R27, R31, R32, R39, R40, R44, R45, R49, R50, R55, R56, R60, R61, R65, R66",0402,24,10,C25077
R17,R2512,1,HOYLR2512E,C5375456
"R18, R2, R23, R28, R36, R4, R41, R46, R52, R57, R62, R7",0402,12,4.7k,C25900
"R34, R35",0402,2,39k,C25783
U1,SOT-89-3_L4.5-W2.5-P1.50-LS4.2-BR,1,HT75C0-1,C64551
"U10, U4, U5, U8",QFN-24_L4.0-W4.0-P0.50-TL-EP2.6,4,EG6288,C55058511
"U11, U3, U6, U9",QFN-20_L3.0-W3.0-P0.50-BL-EP1.7_EFM8BB21F16G,4,EFM8BB21F16G,C80713
U2,SOT-89-3_L4.5-W2.5-P1.50-LS4.2-BR,1,HT7533-1,C14289
U7,SOT-23-5_L3.0-W1.7-P0.95-LS2.8-BR,1,INA139NA,C129947
